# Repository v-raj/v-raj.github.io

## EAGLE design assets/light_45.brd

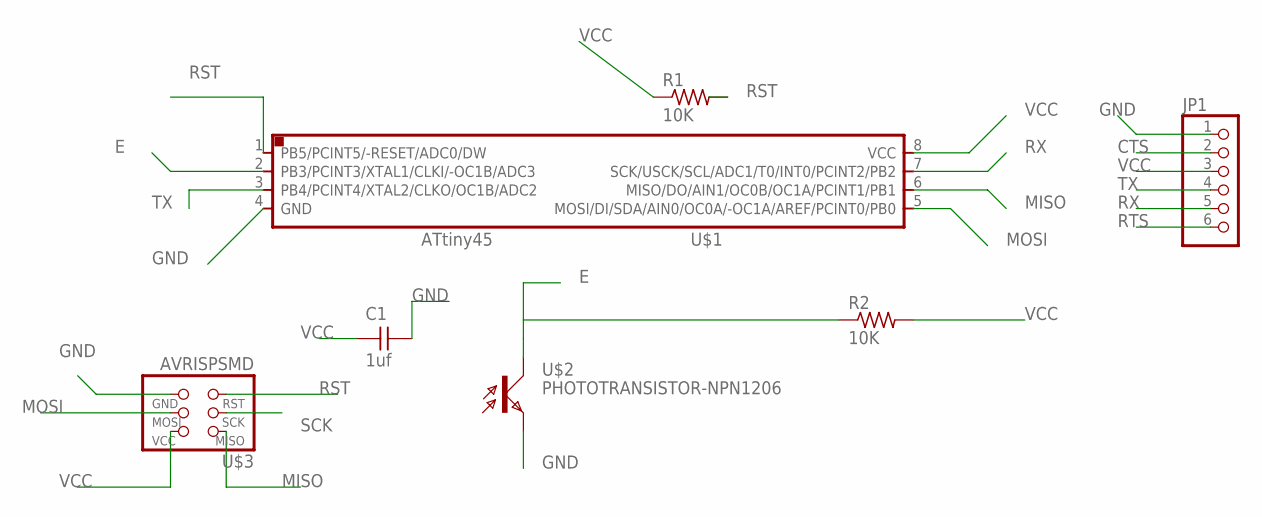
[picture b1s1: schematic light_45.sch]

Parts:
C1: 1uf; 1206
JP1: PINHD-1X6B; 1X06-BIG
R1, R2: 10K; R1206FAB
U$1: ATTINY45SI; SOIC8
U$2: PHOTOTRANSISTOR-NPN1206; OP1206
U$3: AVRISPSMD; 2X03SMD

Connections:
CTS: JP1.2
E: R2.1, U$1.2 (PB3/PCINT3/XTAL1/CLKI/-OC1B/ADC3), U$2.COLLECTOR (C)
GND: C1.2, JP1.1, U$1.4 (GND), U$2.EMITTER (E), U$3.6 (GND)
MISO: U$1.6 (MISO/DO/AIN1/OC0B/OC1A/PCINT1/PB1), U$3.1 (MISO)
MOSI: U$1.5 (MOSI/DI/SDA/AIN0/OC0A/-OC1A/AREF/PCINT0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), U$3.4 (MOSI)
RST: R1.2, U$1.1 (PB5/PCINT5/-RESET/ADC0/DW), U$3.5 (RST)
RTS: JP1.6
RX: JP1.5, U$1.7 (SCK/USCK/SCL/ADC1/T0/INT0/PCINT2/PB2)
SCK: U$3.3 (SCK)
TX: JP1.4, U$1.3 (PB4/PCINT4/XTAL2/CLKO/OC1B/ADC2)
VCC: C1.1, JP1.3, R1.1, R2.2, U$1.8 (VCC), U$3.2 (VCC)

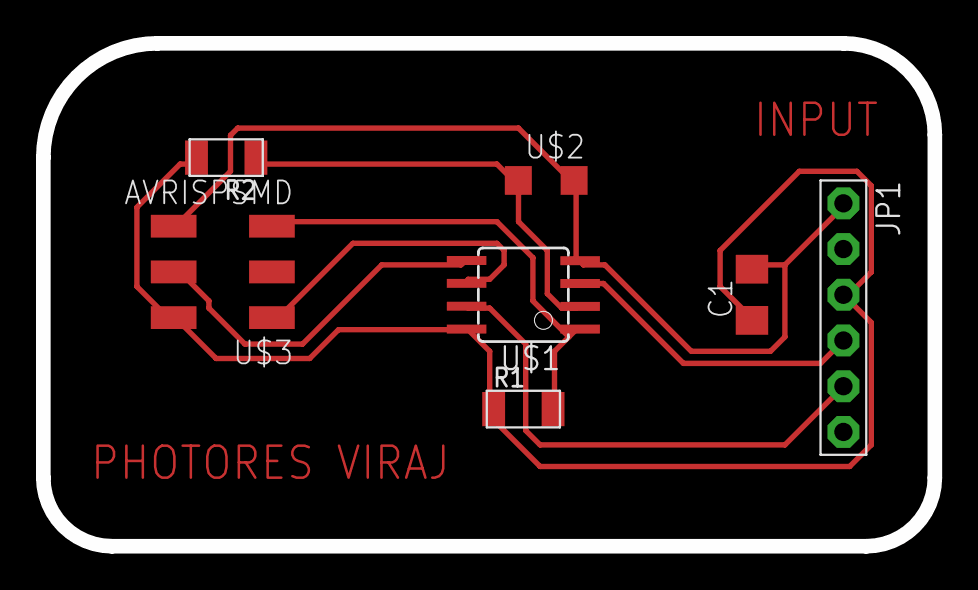
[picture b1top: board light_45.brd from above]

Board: 2 copper layers, 49.5 x 27.9 mm, 7 parts (0 on the bottom side), 8 nets.

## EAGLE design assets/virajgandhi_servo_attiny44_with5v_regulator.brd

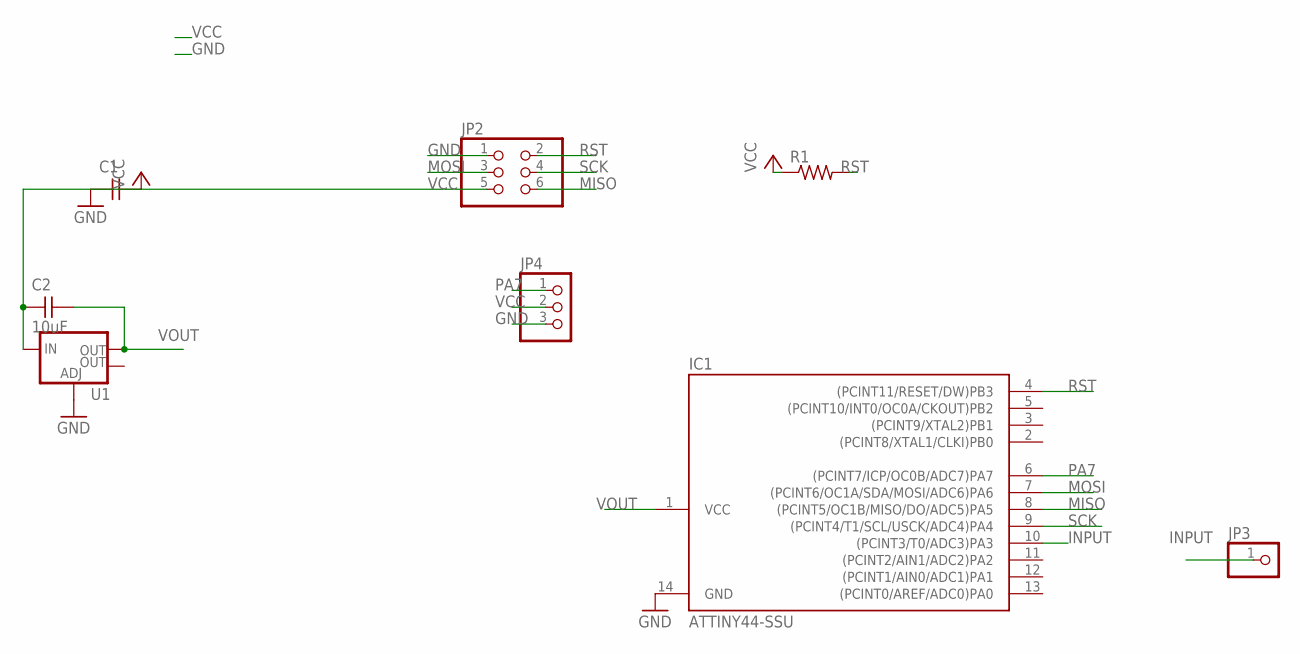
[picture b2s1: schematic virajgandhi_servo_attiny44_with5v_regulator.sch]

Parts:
C1: CAP-UNPOLARIZEDFAB; C1206FAB
C2: 10uF; C1206FAB
IC1: ATTINY44-SSU; SOIC14
JP2: PINHD-2X3-SMD; 2X03SMD
JP3: PINHD-1X1; 1X01
JP4: PINHD-1X3; 1X03
R1: RES-US1206FAB; R1206FAB
U1: V_REG_LM1117SOT223; SOT223

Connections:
GND: C1.1, IC1.14 (GND), JP2.1, JP4.3, U1.1 (ADJ)
INPUT: IC1.10 ((PCINT3/T0/ADC3)PA3), JP3.1
MISO: IC1.8 ((PCINT5/OC1B/MISO/DO/ADC5)PA5), JP2.6
MOSI: IC1.7 ((PCINT6/OC1A/SDA/MOSI/ADC6)PA6), JP2.3
PA7: IC1.6 ((PCINT7/ICP/OC0B/ADC7)PA7), JP4.1
RST: IC1.4 ((PCINT11/RESET/DW)PB3), JP2.2, R1.2
SCK: IC1.9 ((PCINT4/T1/SCL/USCK/ADC4)PA4), JP2.4
VCC: C1.2, C2.1, JP2.5, JP4.2, R1.1, U1.3 (IN)
VOUT: C2.2, IC1.1 (VCC), U1.2 (OUT)

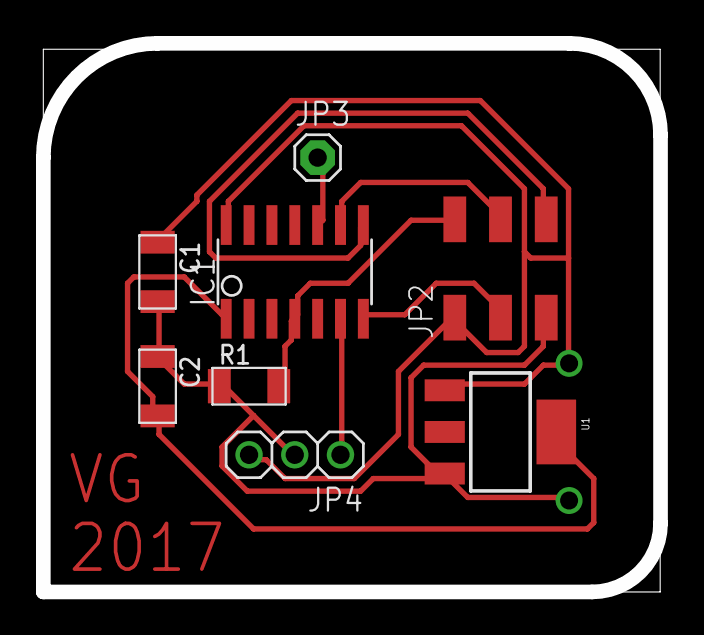
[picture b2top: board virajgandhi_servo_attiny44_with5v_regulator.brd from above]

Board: 2 copper layers, 34.3 x 30.5 mm, 8 parts (0 on the bottom side), 9 nets.

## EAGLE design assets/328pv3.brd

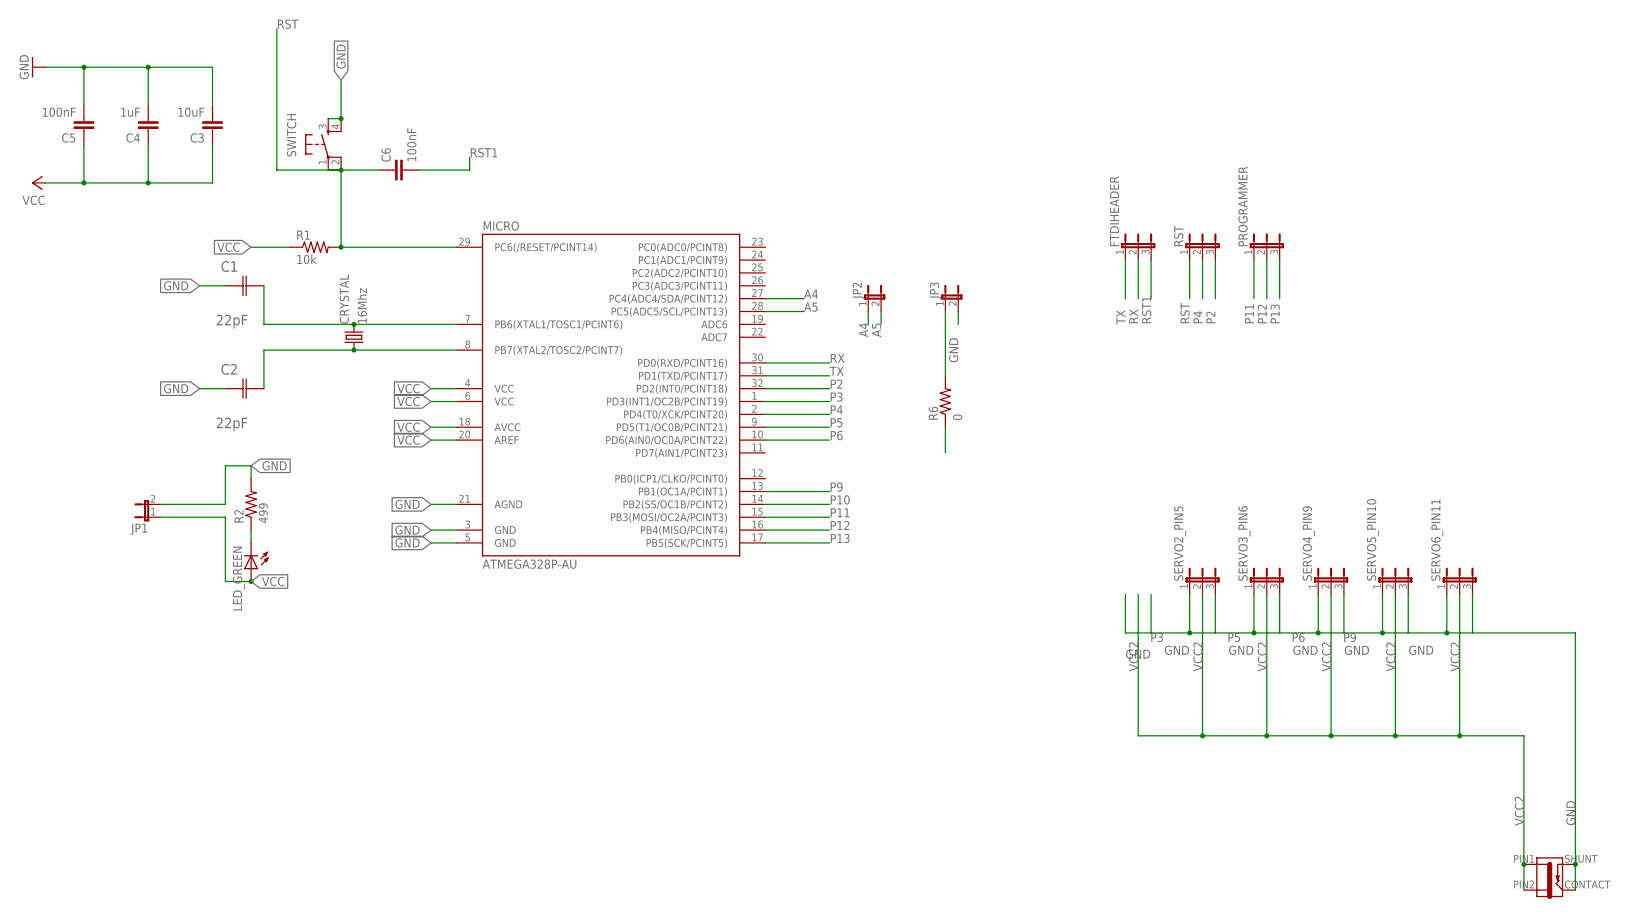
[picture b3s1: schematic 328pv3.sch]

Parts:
C1, C2: 22pF; CAPC3216X178N
C3: 10uF; 1206
C4: 1uF; 1206
C5, C6: 100nF; 1206
CRYSTAL: 16Mhz; CSM-7X-DU
FTDIHEADER: JP2E; JP2
J1: JACK-2.1MM; PJ-002AH-SMT
JP1, JP2, JP3: JP1E; JP1
LED_GREEN: LED1206; 1206
MICRO: ATMEGA328P-AU; TQFP32-08
PROGRAMMER: JP2E; JP2
R1: 10k; 1206
R2: 499; 1206
R6: 0; 1206
RST: JP2E; JP2
SERVO2_PIN5, SERVO3_PIN6, SERVO4_PIN9, SERVO5_PIN10, SERVO6_PIN11: JP2E; JP2
SWITCH: 6MM_SWITCH6MM_SWITCH; 6MM_SWITCH

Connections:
A4: JP2.1, MICRO.27 (PC4(ADC4/SDA/PCINT12))
A5: JP2.2, MICRO.28 (PC5(ADC5/SCL/PCINT13))
GND: C1.1 (C1), C2.1 (C1), C3.2, C4.2, C5.2, J1.CONTACT, J1.SHUNT, JP1.2, JP3.2, MICRO.3 (GND), MICRO.5 (GND), MICRO.21 (AGND), R2.2, SERVO2_PIN5.1, SERVO3_PIN6.1, SERVO4_PIN9.1, SERVO5_PIN10.1, SERVO6_PIN11.1, SWITCH.3 (S), SWITCH.4 (S1)
unnamed: C1.2 (C2), CRYSTAL.2, MICRO.7 (PB6(XTAL1/TOSC1/PCINT6))
unnamed: JP3.1, R6.2
unnamed: C2.2 (C2), CRYSTAL.1, MICRO.8 (PB7(XTAL2/TOSC2/PCINT7))
unnamed: LED_GREEN.2 (C), R2.1
P2: MICRO.32 (PD2(INT0/PCINT18)), RST.3
P3: MICRO.1 (PD3(INT1/OC2B/PCINT19))
P4: MICRO.2 (PD4(T0/XCK/PCINT20)), RST.2
P5: MICRO.9 (PD5(T1/OC0B/PCINT21)), SERVO2_PIN5.3
P6: MICRO.10 (PD6(AIN0/OC0A/PCINT22)), SERVO3_PIN6.3
P9: MICRO.13 (PB1(OC1A/PCINT1)), SERVO4_PIN9.3
P10: MICRO.14 (PB2(SS/OC1B/PCINT2)), SERVO5_PIN10.3
P11: MICRO.15 (PB3(MOSI/OC2A/PCINT3)), PROGRAMMER.1, SERVO6_PIN11.3
P12: MICRO.16 (PB4(MISO/PCINT4)), PROGRAMMER.2
P13: MICRO.17 (PB5(SCK/PCINT5)), PROGRAMMER.3
RST: C6.1, MICRO.29 (PC6(/RESET/PCINT14)), R1.2, RST.1, SWITCH.1, SWITCH.2 (P1)
RST1: C6.2, FTDIHEADER.3
RX: FTDIHEADER.2, MICRO.30 (PD0(RXD/PCINT16))
TX: FTDIHEADER.1, MICRO.31 (PD1(TXD/PCINT17))
VCC: C3.1, C4.1, C5.1, JP1.1, LED_GREEN.1 (A), MICRO.4 (VCC), MICRO.6 (VCC), MICRO.18 (AVCC), MICRO.20 (AREF), R1.1
VCC2: J1.PIN1, J1.PIN2, R6.1, SERVO2_PIN5.2, SERVO3_PIN6.2, SERVO4_PIN9.2, SERVO5_PIN10.2, SERVO6_PIN11.2

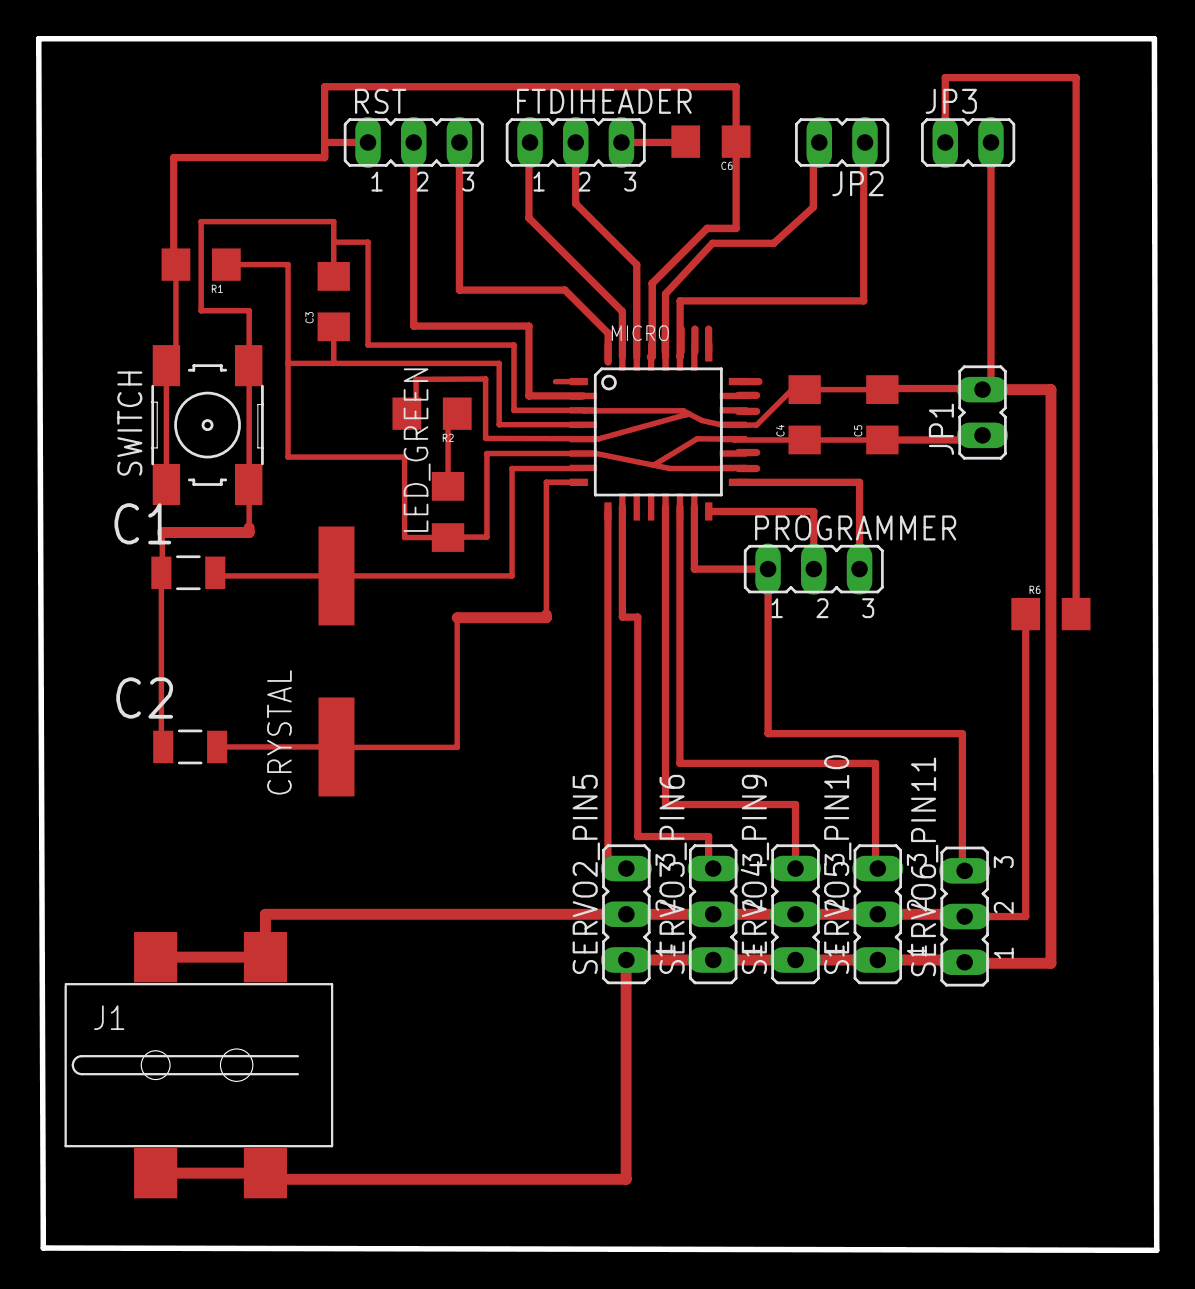
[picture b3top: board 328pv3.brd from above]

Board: 2 copper layers, 62.1 x 67.3 mm, 25 parts (0 on the bottom side), 22 nets.

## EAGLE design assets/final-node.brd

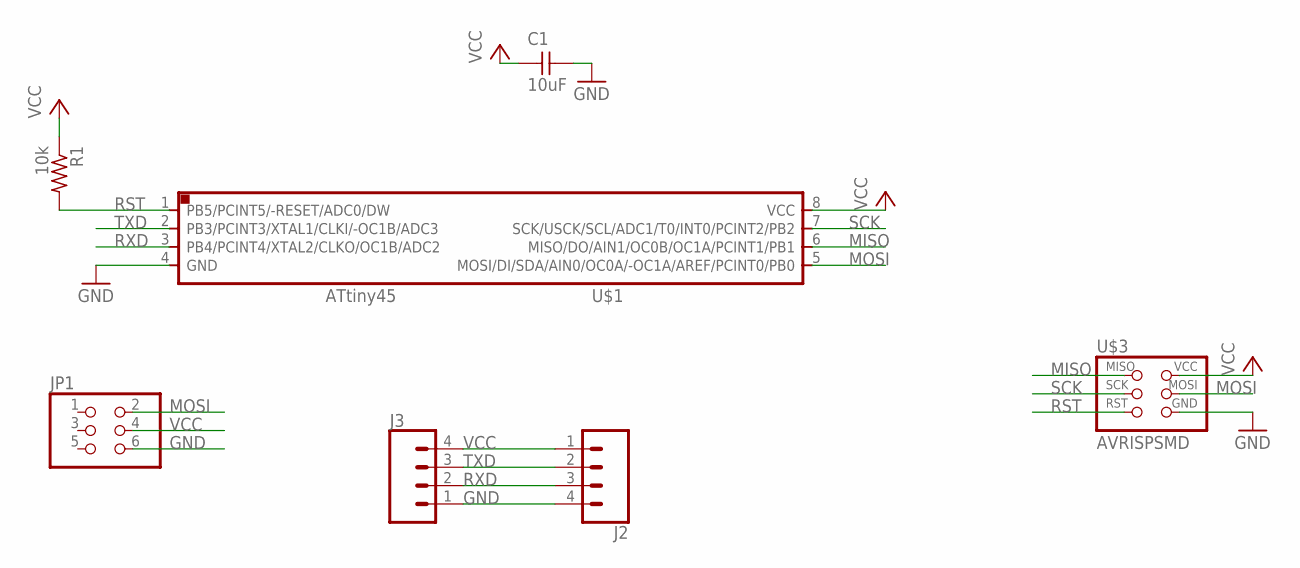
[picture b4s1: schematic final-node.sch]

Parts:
C1: 10uF; C1206FAB
J2, J3: CONN_04SMD; 1X04_SMD_RA_MALE
JP1: PINHD-2X3-SMD; 2X03SMD
R1: 10k; R1206FAB
U$1: ATTINY45SI; SOIC8
U$3: AVRISPSMD; 2X03SMD

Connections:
GND: C1.2, J2.4, J3.1, JP1.6, U$1.4 (GND), U$3.6 (GND)
MISO: U$1.6 (MISO/DO/AIN1/OC0B/OC1A/PCINT1/PB1), U$3.1 (MISO)
MOSI: JP1.2, U$1.5 (MOSI/DI/SDA/AIN0/OC0A/-OC1A/AREF/PCINT0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), U$3.4 (MOSI)
RST: R1.2, U$1.1 (PB5/PCINT5/-RESET/ADC0/DW), U$3.5 (RST)
RXD: J2.3, J3.2, U$1.3 (PB4/PCINT4/XTAL2/CLKO/OC1B/ADC2)
SCK: U$1.7 (SCK/USCK/SCL/ADC1/T0/INT0/PCINT2/PB2), U$3.3 (SCK)
TXD: J2.2, J3.3, U$1.2 (PB3/PCINT3/XTAL1/CLKI/-OC1B/ADC3)
VCC: C1.1, J2.1, J3.4, JP1.4, R1.1, U$1.8 (VCC), U$3.2 (VCC)

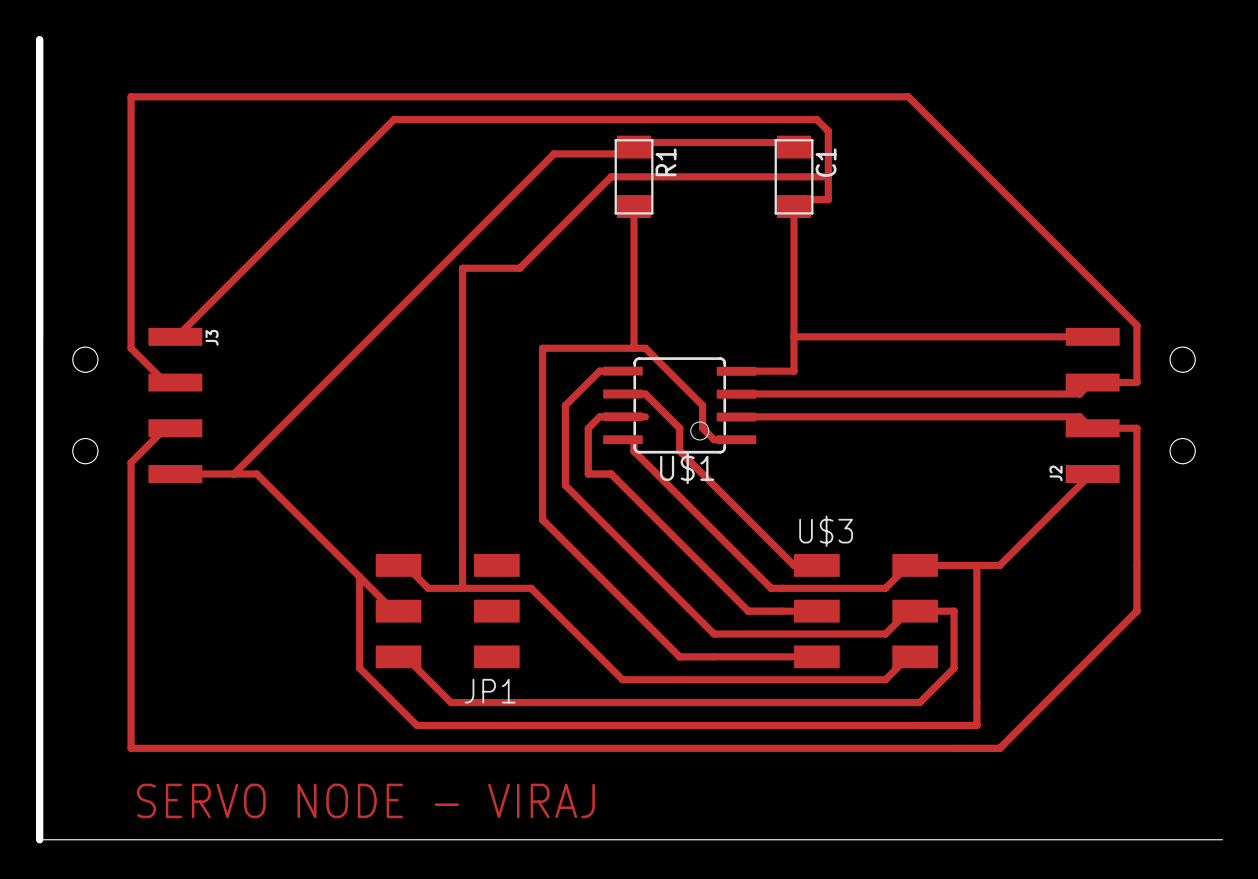
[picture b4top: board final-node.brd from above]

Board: 2 copper layers, 65.5 x 44.4 mm, 7 parts (0 on the bottom side), 8 nets.

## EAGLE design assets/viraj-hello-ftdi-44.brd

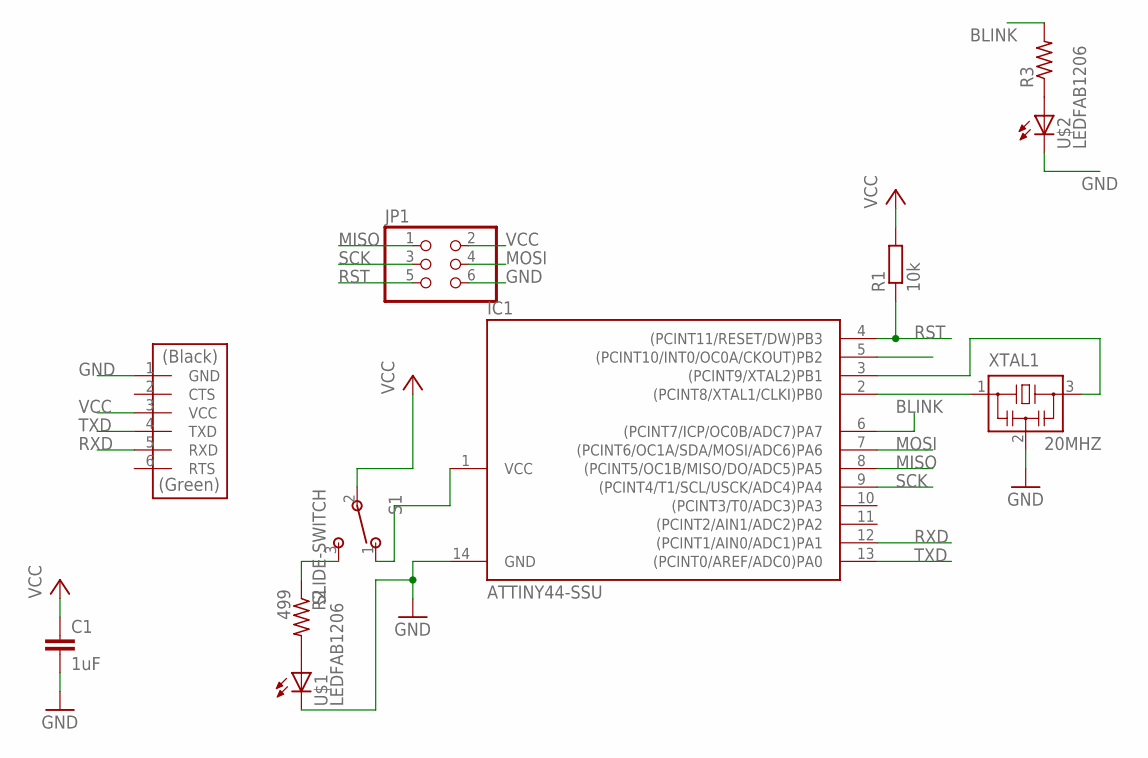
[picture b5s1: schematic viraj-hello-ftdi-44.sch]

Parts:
C1: 1uF; C1206
IC1: ATTINY44-SSU; SOIC14
J2: FTDI-SMD-HEADER; 1X06SMD
JP1: PINHD-2X3-SMD; 2X03SMD
R1: 10k; M1206
R2: 499; R1206FAB
R3: RES-US1206FAB; R1206FAB
S1: SLIDE-SWITCH; AYZ0102AGRLC
U$1, U$2: LEDFAB1206; LED1206FAB
XTAL1: 20MHZ; EFOBM

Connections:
BLINK: IC1.6 ((PCINT7/ICP/OC0B/ADC7)PA7), R3.2
GND: C1.2, IC1.14 (GND), J2.1 (GND), JP1.6, U$1.2 (C), U$2.2 (C), XTAL1.2
MISO: IC1.8 ((PCINT5/OC1B/MISO/DO/ADC5)PA5), JP1.1
MOSI: IC1.7 ((PCINT6/OC1A/SDA/MOSI/ADC6)PA6), JP1.4
unnamed: IC1.1 (VCC), S1.1
unnamed: R2.1, S1.3
unnamed: R2.2, U$1.1 (A)
unnamed: R3.1, U$2.1 (A)
unnamed: IC1.2 ((PCINT8/XTAL1/CLKI)PB0), XTAL1.1
unnamed: IC1.3 ((PCINT9/XTAL2)PB1), XTAL1.3
RST: IC1.4 ((PCINT11/RESET/DW)PB3), JP1.5, R1.1
RXD: IC1.12 ((PCINT1/AIN0/ADC1)PA1), J2.5 (RXD)
SCK: IC1.9 ((PCINT4/T1/SCL/USCK/ADC4)PA4), JP1.3
TXD: IC1.13 ((PCINT0/AREF/ADC0)PA0), J2.4 (TXD)
VCC: C1.1, J2.3 (VCC), JP1.2, R1.2, S1.2

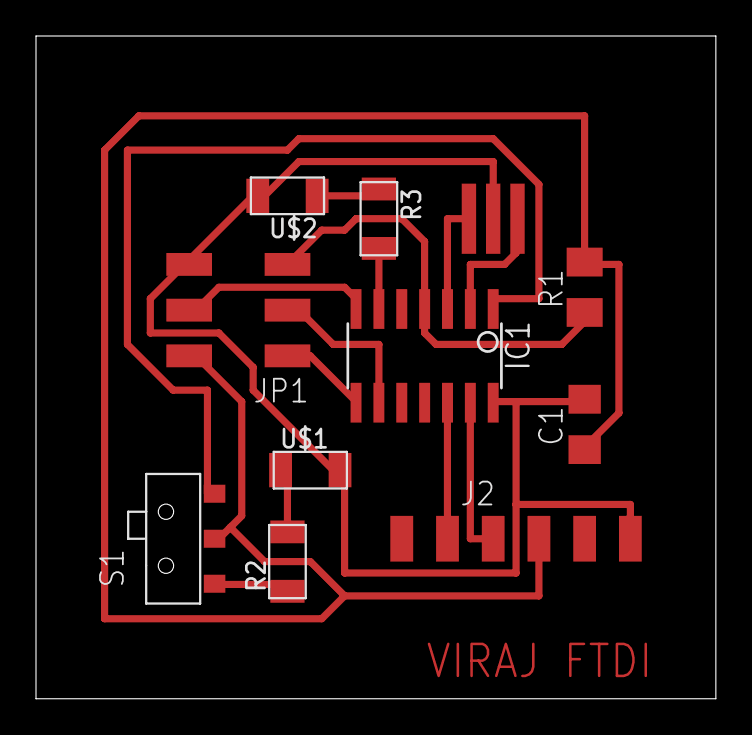
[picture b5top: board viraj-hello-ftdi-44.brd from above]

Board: 2 copper layers, 37.8 x 36.8 mm, 11 parts (0 on the bottom side), 15 nets.

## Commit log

2017-10-28 Viraj Upload
2017-11-01 Pasting from Fab last push
2017-11-01 link local relative
2017-11-01 deleted the Presentation.png
2017-11-01 added presentation.png
2017-11-01 deleted p file
2017-11-01 p file added
2017-11-01 deleted file p
2017-11-01 added p again

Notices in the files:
parts and their libraries:
01_SparkFun: Licensing: CC v3.0 Share-Alike You are welcome to use this library for commercial purposes.
SparkFun-Connectors: Licensing: Creative Commons ShareAlike 4.0 International - https://creativecommons.org/licenses/by-sa/4.0
